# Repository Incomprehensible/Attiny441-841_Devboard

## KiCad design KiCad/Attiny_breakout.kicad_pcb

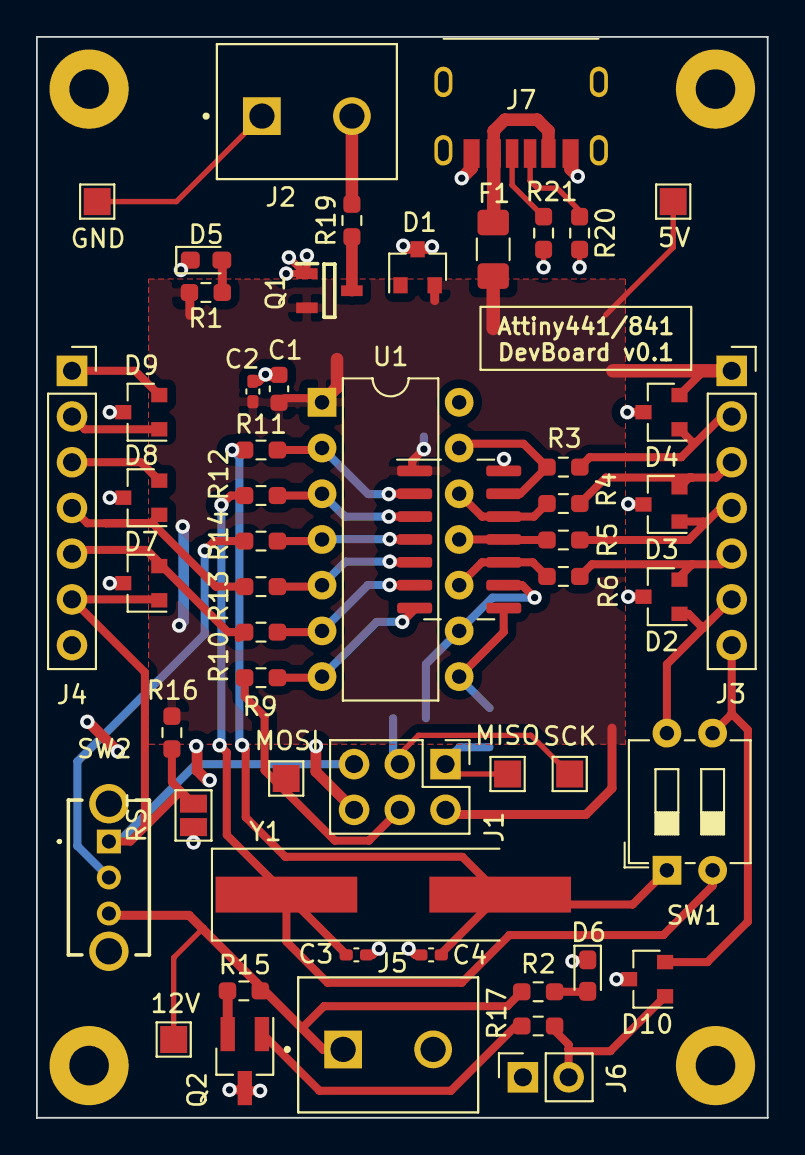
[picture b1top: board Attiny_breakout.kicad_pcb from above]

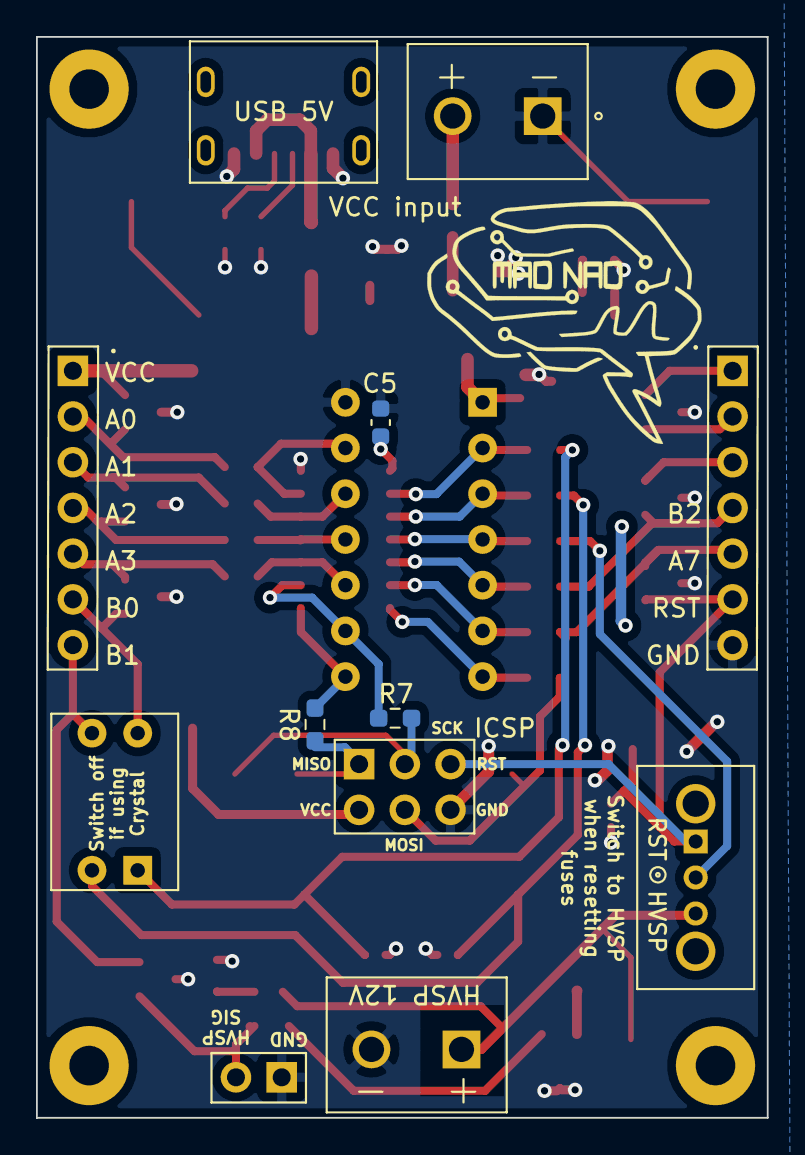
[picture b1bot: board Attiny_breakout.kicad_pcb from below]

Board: 2 copper layers, 40.6 x 60.0 mm, 60 parts (3 on the bottom side), 43 nets.

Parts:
C1, C5: 10uF; C_0603_1608Metric
C2: C_reserve; C_0402_1005Metric_Pad0.74x0.62mm_HandSolder
C3, C4: C; C_0402_1005Metric_Pad0.74x0.62mm_HandSolder
D1, D2, D3, D4, D7, D8, D9, D10: ESDA5V3L; SOT-23
D5: PWR_STATUS; LED_0603_1608Metric_Pad1.05x0.95mm_HandSolder
D6: 12V_STATUS; LED_0603_1608Metric_Pad1.05x0.95mm_HandSolder
F1: Fuse; Fuse_1206_3216Metric_Pad1.42x1.75mm_HandSolder
H1, H2, H3, H4: MountingHole; MountingHole_2.2mm_M2_Pad
J1: ICSP; PinHeader_2x03_P2.54mm_Vertical
J2: PowerConn; HANDSON_KF301-2P
J3, J4: Conn_01x07_Female; PinSocket_1x07_P2.54mm_Vertical
J5: 12V_conn; HANDSON_KF301-2P
J6: HVP_EN_conn; PinSocket_1x02_P2.54mm_Vertical
J7: USB_C_Receptacle_USB2.0; usb_c_receptable_hro_type-c-31-m-17
JP1: RST; SolderJumper-2_P1.3mm_Open_Pad1.0x1.5mm
Q1: AO3401A; SOT95P280X125-3N
Q2: BC847C; SOT-23_Handsoldering
R1: 1k; R_0603_1608Metric_Pad0.98x0.95mm_HandSolder
R2, R16: 10k; R_0603_1608Metric_Pad0.98x0.95mm_HandSolder
R3, R4, R5, R6, R7, R8, R9, R10, R11, R12, R13, R14: R_0; R_0603_1608Metric_Pad0.98x0.95mm_HandSolder
R15: R_coll; R_0603_1608Metric_Pad0.98x0.95mm_HandSolder
R17: R_gate; R_0603_1608Metric_Pad0.98x0.95mm_HandSolder
R19: R_inrush; R_0603_1608Metric_Pad0.98x0.95mm_HandSolder
R20, R21: 5.1k; R_0603_1608Metric_Pad0.98x0.95mm_HandSolder
SW1: SW_DIP_x02; SW_DIP_SPSTx02_Slide_6.7x6.64mm_W7.62mm_P2.54mm_LowProfile
SW2: Normal vs HVSP mode; SS12D07L4B
TP1: 5V; TestPoint_Pad_1.5x1.5mm
TP2: GND; TestPoint_Pad_1.5x1.5mm
TP3: MOSI; TestPoint_Pad_1.5x1.5mm
TP4: MISO; TestPoint_Pad_1.5x1.5mm
TP5: SCK; TestPoint_Pad_1.5x1.5mm
TP6: 12V; TestPoint_Pad_1.5x1.5mm
U1: ATtiny441-SSU; DIP-14_W7.62mm_SOIC-14
Y1: Crystal; Crystal_SMD_HC49-SD_HandSoldering

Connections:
A0: D4.1, J3.2, R3.1
A1: D3.2, J3.3, R4.1
A2: D3.1, J3.4, R5.1
A3: D2.2, J3.5, R6.1
A7: D7.2, J4.5, R10.1
B0_XTAL1: C4.1, R11.1, SW1.1, Y1.2
B1_XTAL2: C3.1, R12.1, SW1.2, Y1.1
B2: D8.1, J4.4, R13.1
GND: C1.2, C2.2, C3.2, C4.2, C5.2, D1.3, D2.3, D3.3, D4.3, D5.1, D6.1, D7.3, D8.3, D9.3, D10.3, J1.6, J2.1, J4.7, J5.2, J6.1, J7.A12, J7.B12, JP1.1, Q1.1, Q2.3, R20.2, R21.2, TP2.1, U1.14
HVSP: J5.1, R2.2, R15.2, SW2.3, TP6.1
HVSP_RST: D10.1, J6.2, R17.2
MISO: J1.1, R8.1, TP4.1
MOSI: J1.4, R9.1, TP3.1
unnamed: D2.1, J3.6, SW1.4
unnamed: D5.2, R1.1
unnamed: D6.2, R2.1
unnamed: D8.2, J4.3
unnamed: D9.1, J4.2
unnamed: D9.2, J4.1
unnamed: D10.2, J3.7, SW1.3
unnamed: F1.2, J7.A9, J7.B9
unnamed: J2.2, R19.2
unnamed: J7.A5, R20.1
unnamed: J7.B5, R21.1
unnamed: Q1.3, R19.1
unnamed: Q2.1, R17.1
unnamed: Q2.2, R15.1
unnamed: R3.2, U1.13
unnamed: R4.2, U1.12
unnamed: R5.2, U1.11
unnamed: R6.2, U1.10
unnamed: R7.2, U1.9
unnamed: R8.2, U1.8
unnamed: R9.2, U1.7
unnamed: R10.2, U1.6
unnamed: R11.2, U1.2
unnamed: R12.2, U1.3
unnamed: R13.2, U1.5
unnamed: R14.1, SW2.2
unnamed: R14.2, U1.4
RST: D7.1, J1.5, J4.6, JP1.2, R16.2, SW2.1
SCK: J1.3, R7.1, TP5.1
VCC: C1.1, C2.1, C5.1, D1.2, D4.2, F1.1, J1.2, J3.1, Q1.2, R1.2, R16.1, TP1.1, U1.1

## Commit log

2022-02-20 Version with different SPI pins selection. Under-routed. Next multiple choice will be removed.
2022-02-21 Final version of PCB. Removed unnecessary SPI connections.
